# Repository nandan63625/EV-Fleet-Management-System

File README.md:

## Overview

EV Fleet Guardian is an IoT-based automotive telematics system designed for real-time monitoring and management of electric vehicle fleets.

The system collects vehicle telemetry through the CAN bus, tracks vehicle location using GPS, monitors battery parameters, and uploads data to the cloud for fleet monitoring and analytics.

## Features

* Real-time vehicle tracking
* CAN Bus vehicle data acquisition
* Battery monitoring
* Driver behavior analysis
* GPS geofencing
* GSM-based remote communication
* Custom PCB design
* Automotive power management

## Hardware Components

* ESP32
* MCP2515 CAN Controller
* TJA1050 CAN Transceiver
* NEO-6M GPS Module
* SIM800L GSM Module
* MPU6050 IMU
* MP1584 Buck Converter
* TP4056 Charging Module

## PCB Design

| Top 3D Render | Isometric View |
|---|---|
|  |  |

**PCB Layout (Top Copper + Silkscreen)**

Full KiCad source files: [`Hardware/KiCad-Source/`](Hardware/KiCad-Source/)

Manufacturing files (Gerbers + drill files): [`Hardware/PCB-Gerbers/EV_Guardian_Carrier_Gerbers.zip`](Hardware/PCB-Gerbers/EV_Guardian_Carrier_Gerbers.zip)

## Communication Protocols

* CAN Bus
* SPI
* I2C
* UART
* AT Commands

## Project Structure

* Documentation
* Hardware Design
* PCB Files
* Schematics

## Current Status

Prototype Development and Validation

## Future Improvements

* Predictive Battery Health Analytics
* Cloud Dashboard
* Mobile Application
* Fleet Performance Analytics

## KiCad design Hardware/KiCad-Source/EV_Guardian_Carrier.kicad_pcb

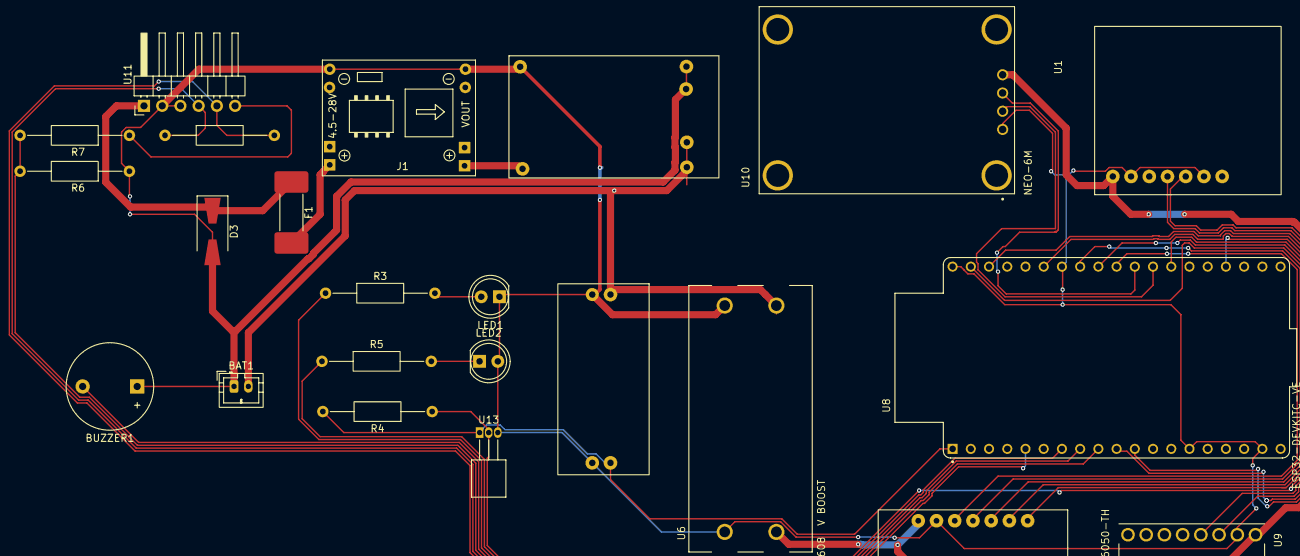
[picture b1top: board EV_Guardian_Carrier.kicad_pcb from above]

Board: 2 copper layers, 23 parts (0 on the bottom side), 26 nets.

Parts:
BAT1: 5v Lion battery; JST_PH_B2B-PH-K_1x02_P2.00mm_Vertical
BUZZER1: buzzer; Buzzer_12x9.5RM7.6
D3: TVS Diode; D_SMA-SMB_Universal_Handsoldering
F1: FUSE; Fuse_Schurter_UMZ250
J1: mp1584; SRT_MPT1584EN_Module
LED1: KT-0805G; LED_D5.0mm
LED2: NCD0805R1; LED_D5.0mm
R2: 120Ω; R_Axial_DIN0207_L6.3mm_D2.5mm_P15.24mm_Horizontal
R3, R5: 220; R_Axial_DIN0207_L6.3mm_D2.5mm_P15.24mm_Horizontal
R4: 4.7K; R_Axial_DIN0207_L6.3mm_D2.5mm_P15.24mm_Horizontal
R6: 100K; R_Axial_DIN0207_L6.3mm_D2.5mm_P15.24mm_Horizontal
R7: 33K; R_Axial_DIN0207_L6.3mm_D2.5mm_P15.24mm_Horizontal
U1: SIM800L; Untitled
U2: AMS1117-3.3; Untitled_2
U3: TP4056; Untitled_1
U5: MCP2515T-E/ML; Untitled
U6: MT3608 V BOOST; MODULE_MT3608_DC-DC_STEP_UP_CONVERTER_2A_BOOSTER_MODULE
U8: ESP32-DEVKITC-VE; MODULE_ESP32-DEVKITC-32E
U9: MPU6050-TH; MODULE_OC09600
U10: NEO-6M; XCVR_ZC323200
U11: OBD Port; PinHeader_1x06_P2.54mm_Horizontal
U13: DS1B20(Tempertaure sensore); TO-92_Inline_Horizontal1

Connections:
3v: R4.2, U2.3 (VIN), U8.J2_1, U13.1
5v: U1.1 (VBAT_1), U5.7 (OSC1_7), U6.VOUT_N, U9.VCC, U10.4 (EXTINT0_4)
/CANH: R2.1, U11.4
/CANL: R2.2, U11.5
/Pin_3: J1.3, U3.2 (PROG)
D21: U8.J3_6, U9.SDA
D23: U5.3 (TX1RTS#_3), U8.J3_2
D25: BUZZER1.2 (+), U8.J2_9
D26: U1.GPIO19 (STATUS_4), U8.J2_10
D27: U1.GPYO23 (BPI_BUS1_5), U8.J2_11
D32: R5.1, U8.J2_7
D33: R3.d (1_1), U8.J2_8
D34: R6.2, R7.2, U8.J2_5
GND: BAT1.1, BUZZER1.1 (-), D3.2 (A), J1.2, J1.4, LED1.1 (A), LED2.2 (+), R6.1, U1.2 (GND_2), U2.2 (VOUT), U2.4 (VOUT), U3.1 (TEMP), U3.3 (GND), U3.4 (VCC), U5.gnd (OSC2_6), U6.VIN_P, U6.VOUT_P, U8.J2_14, U8.J2_18, U8.J3_1, U8.J3_7, U9.GND, U10.1 (Reserved_1), U11.2, U11.3, U13.3
unnamed: LED1.2 (K), R3.2 (2_2)
unnamed: LED2.1 (-), R5.2
batterypos: BAT1.2, U2.1 (GND), U3.5 (BAT), U3.6 (STDBY), U6.VIN_N
d4: U5.int (CLKOUT_1), U8.J3_13
d5: U5.5 (TX2RTS#_5), U8.J3_10
d15: R4.1, U8.J3_16, U13.2
d16: U8.J3_12, U10.TX (SS_N_2)
d17: U8.J3_11, U10.RX (TIMEPULSE_3)
d18: U5.d1 (TX0RTS#_2), U8.J3_9
d22: U8.SCL, U9.SCL
ignitob: R7.1, U11.6
mainpower12v: D3.1 (K), F1.12 (1_1), U11.1

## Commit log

2026-06-08 Add initial project documentation
2026-06-08 Add README for circuit schematics and design files
2026-06-18 Revise README for EV Fleet Guardian project
    Expanded project details and added features, hardware components, communication protocols, project structure, current status, and future improvements.
2026-06-18 Update README to remove project title
    Removed project title from README.
2026-06-19 Add KiCad source files and Gerber/drill files for EV Guardian Carrier PCB
2026-06-19 Add PCB layout SVGs and 3D render images
2026-06-19 Add PCB images to README
2026-06-19 Fix README - restore content and add PCB section
2026-06-19 Remove empty placeholder PCB_Design folder
2026-06-19 Remove empty PCB_Design folder and stray paste-layer export
2026-06-19 Remove redundant Schematics README
